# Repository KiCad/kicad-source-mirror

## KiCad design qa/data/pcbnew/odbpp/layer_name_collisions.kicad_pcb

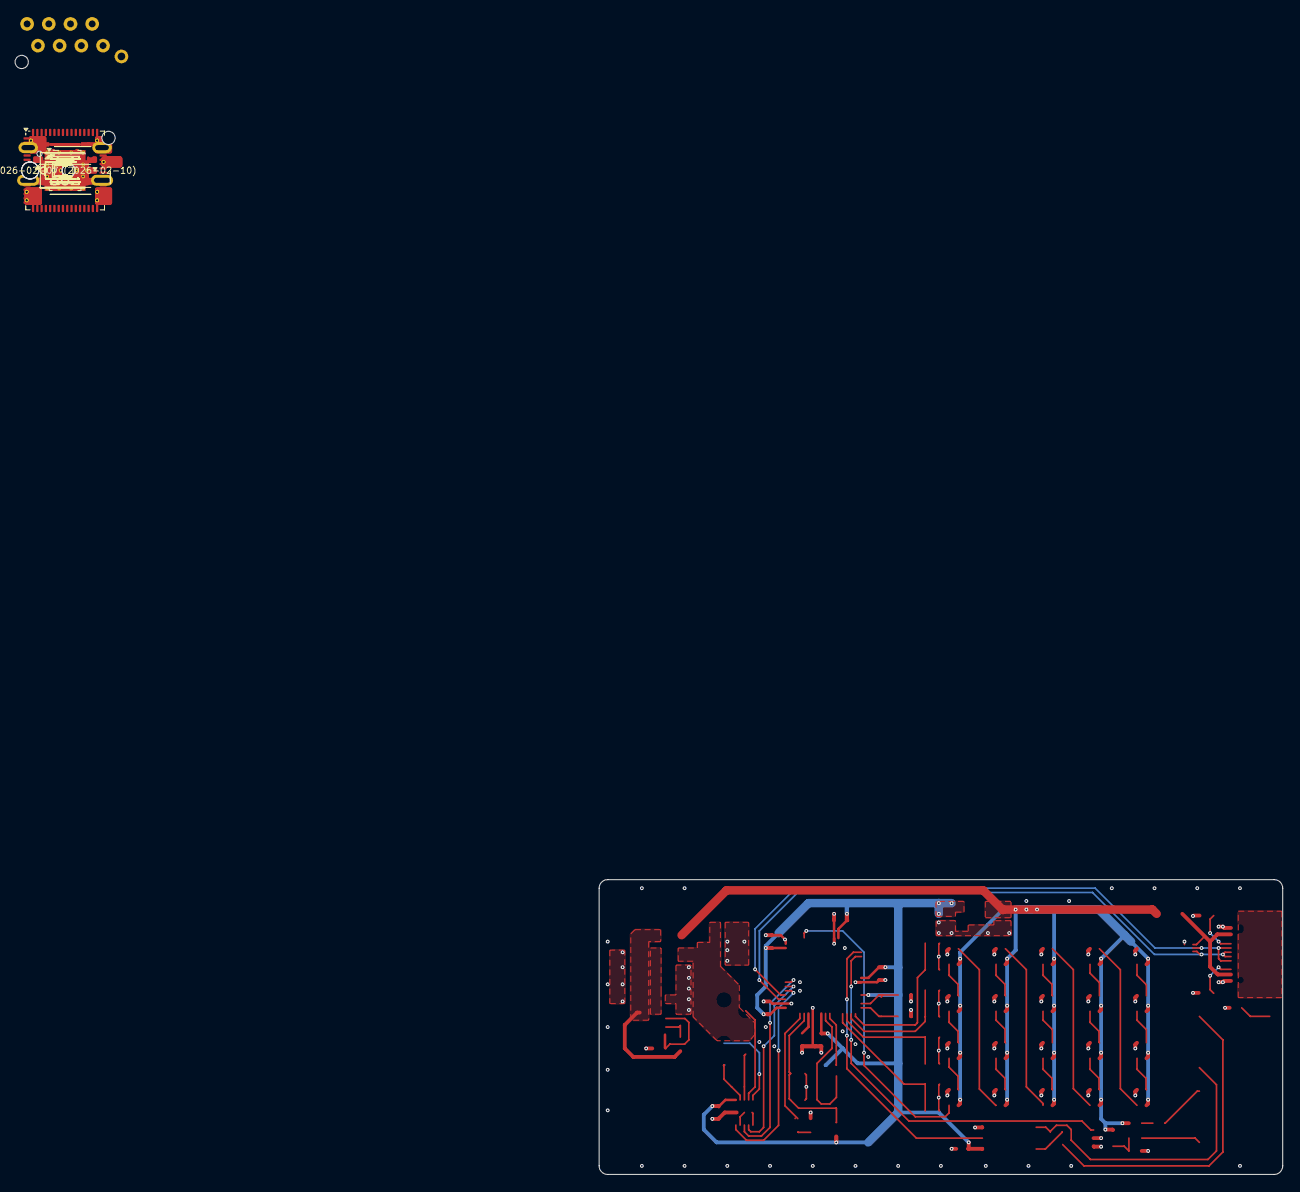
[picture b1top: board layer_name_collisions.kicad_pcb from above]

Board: 4 copper layers, 80.0 x 34.5 mm, 81 parts (1 on the bottom side), 62 nets.

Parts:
C101: 10u; C_0603
C102, C103, C104, C105, C106, C111, C201, C301, C302, C1202: 0u1; C_0603
C107, C110: 18p; C_0603
C108, C109: 10u; C_0805
C1201: 10u; C_1210
C1203, C1204: 22u; C_1210
C1205: 1u; C_0603
D101: Orange; LED_0603
D102, D103, D104: PMEG6030AEXEX; D_SOD-123HP
D301, D401: RB501SM; D_SOD-523
D501, D502, D503, D504, D505, D506, D507, D508, D509, D510, D511, D512, D513, D514, D515, D516, D517, D518, D519, D520: WS2812; WS2812-2020
ESD101: RCLAMP0582N; SLP1210N6
FID101, FID102, FID103: Fiducial_Paste; Fiducial_0.5mm_Mask1mm_Paste
ICON101: V2-logo; Logo_Small
INFO101: Revision
INFO102: Layer_Numbers
J101: Cortex
J102: DX07S016JA3; JAE_DX07S016JA3
J201: NE8FAH
J301, J401: SJ2-25404B-SMT-TR; CUI_SJ2-25404B-SMT-TR
R101: 330R; R_0603
R102, R103: 5k1; R_0603
R104: 100k; R_0603
R201: 100R; R_0603
R301, R401, R402: 220R; R_0603
R1201: 40k2; R_0603
R1202: 10k; R_0603
SW101, SW102, SW103, SW104, SW105: SKSG
TVS101: SMBJ33CA; D_SMB
TVS401: CG0603MLC-05LE; D_0603
U101: TPS78433QWDRBRQ1; VSON-8-1_3x3mm_P0.65_EP1.65x2.4mm
U102: ATSAMD51J; QFN-64-1EP_9x9mm_P0.5mm_EP4.8x4.8mm_ThermalVias
U201: THVD2442; VSON-10-4-1EP_3x3mm_P0.5mm_EP1.65x2.4mm_ThermalVias
U301: TLP2361; SO-5-6_4.55x3.7mm_P1.27mm
U401: 74AHC1G125; SOT-23-5
U1201: TPSM365R6FRDNR; QFN-11
Y101: 32k768; Crystal_SMD_3215-2Pin_3.2x1.5mm

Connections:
+3V3: C102.1, C103.1, C104.1, C105.1, C106.1, C109.1, C201.1, C301.1, J101.1 (VCC), R104.1, U101.1 (OUT), U102.4 (ANAREF), U102.8 (VDDANA), U102.21 (VDDIOB), U102.34 (VDDIO), U102.48 (VDDIO), U102.56 (VDDIO), U201.10 (VCC), U301.6 (VDD)
+5V: C108.1, D102.1 (K), D103.1 (K), D501.4 (VCC), D502.4 (VCC), D503.4 (VCC), D504.4 (VCC), D505.4 (VCC), D506.4 (VCC), D507.4 (VCC), D508.4 (VCC), D509.4 (VCC), D510.4 (VCC), D511.4 (VCC), D512.4 (VCC), D513.4 (VCC), D514.4 (VCC), D515.4 (VCC), D516.4 (VCC), D517.4 (VCC), D518.4 (VCC), D519.4 (VCC), D520.4 (VCC), R401.2, U101.7 (EN), U101.8 (IN), U401.5
+VLINK: C111.1, D104.2 (A), J201.4, J201.5, TVS101.2 (A)
/+5V-Link: C1203.1, C1204.1, D103.2 (A), R1201.1, U1201.4 (VOUT)
/+VBUS: D102.2 (A), ESD101.6 (VBUS), J102.V (VBUS)
/+VLINK-Supply: C1201.1, C1202.1, D104.1 (K), U1201.2 (EN), U1201.3 (VIN)
/Button-1: SW101.2, U102.61 (PB00)
/Button-2: SW102.2, U102.62 (PB01)
/Button-3: SW103.2, U102.63 (PB02)
/Button-4: SW104.2, U102.64 (PB03)
/LED-Onboard: D101.2 (A), U102.51 (PA27)
/LEDs: D501.3 (IN), U102.29 (PA12)
/LEDs/LED-5: D504.1 (OUT), D505.3 (IN)
/LEDs/LED-9: D508.1 (OUT), D509.3 (IN)
/LEDs/LED-13: D512.1 (OUT), D513.3 (IN)
/LEDs/LED-17: D516.1 (OUT), D517.3 (IN)
/Link Socket/RX-A: J201.1, R201.1, U201.9 (A)
/Link Socket/RX-B: J201.2, R201.2, U201.8 (B)
/Link Socket/TX-Y: J201.3, U201.6 (Y)
/Link Socket/TX-Z: J201.6, U201.7 (Z)
/MIDI In/Ring: J301.3 (R1), R301.1
/MIDI In/Sleeve: C302.1, J301.1 (S)
/MIDI In/Tip: D301.2 (A), J301.2 (T), U301.3 (K)
/MIDI Out/Ring: D401.1 (K), J401.3 (R1)
/MIDI Out/Tip: J401.2 (T), R402.2
/MIDI-In: U102.14 (PA05), U301.5 (VO)
/MIDI-Out: U102.13 (PA04), U401.1
/Power +5V/Feedback: R1201.2, R1202.1, U1201.9 (FB)
/Power +5V/Vcc: C1205.1, U1201.8 (VCC), U1201.11 (MODE)
/RESET: J101.10 (RESET), R104.2, SW105.2, U102.52 (~RESET)
/SWCLK: J101.4 (SWCLK), U102.57 (PA30)
/SWDIO: J101.2 (SWDIO), U102.58 (PA31)
/Socket-RX: U102.44 (PA23), U201.1 (R)
/Socket-TX: U102.43 (PA22), U201.4 (D)
/Socket-TX-Enable: U102.42 (PA21), U201.3 (DE)
/USB+: ESD101.4 (I/O1), J102.A6 (D+), J102.B6 (D+), U102.46 (USB+)
/USB-: ESD101.5 (I/O2), J102.A7 (D-), J102.B7 (D-), U102.45 (USB-)
/USB-CC1: J102.A5 (CC1), R102.1
/USB-CC2: J102.B5 (CC2), R103.1
/VDDCORE: C101.1, U102.53 (VDDCORE)
/XIN32: C107.1, U102.1 (PA00), Y101.2
/XOUT32: C110.1, U102.2 (PA01), Y101.1
GND: C101.2, C102.2, C103.2, C104.2, C105.2, C106.2, C107.2, C108.2, C109.2, C110.2, C111.2, C201.2, C301.2, C302.2, C1201.2, C1202.2, C1203.2, C1204.2, C1205.2, D501.2 (GND), D502.2 (GND), D503.2 (GND), D504.2 (GND), D505.2 (GND), D506.2 (GND), D507.2 (GND), D508.2 (GND), D509.2 (GND), D510.2 (GND), D511.2 (GND), D512.2 (GND), D513.2 (GND), D514.2 (GND), D515.2 (GND), D516.2 (GND), D517.2 (GND), D518.2 (GND), D519.2 (GND), D520.2 (GND), ESD101.1 (GND), J101.3 (GND), J101.5 (GND), J102.G (GND), J201.7, J201.8, J401.1 (S), R101.2, R102.2, R103.2, R1202.2, SW101.1, SW102.1, SW103.1, SW104.1, SW105.1, TVS101.1 (K), TVS401.1 (K), U101.5 (GND), U101.9 (GND), U102.7 (GNDANA), U102.22 (GND), U102.33 (GND), U102.47 (GND), U102.54 (GND), U102.65 (PAD), U201.2 (RE), U201.5 (GND), U201.11 (GND), U301.4 (GND), U401.2, U401.3, U1201.10 (GND)
unnamed: D101.1 (K), R101.1
unnamed: D301.1 (K), R301.2, U301.1 (A)
unnamed: D401.2 (A), R401.1
unnamed: D501.1 (OUT), D502.3 (IN)
unnamed: D502.1 (OUT), D503.3 (IN)
unnamed: D503.1 (OUT), D504.3 (IN)
unnamed: D505.1 (OUT), D506.3 (IN)
unnamed: D506.1 (OUT), D507.3 (IN)
unnamed: D507.1 (OUT), D508.3 (IN)
unnamed: D509.1 (OUT), D510.3 (IN)
unnamed: D510.1 (OUT), D511.3 (IN)
unnamed: D511.1 (OUT), D512.3 (IN)
unnamed: D513.1 (OUT), D514.3 (IN)
unnamed: D514.1 (OUT), D515.3 (IN)
unnamed: D515.1 (OUT), D516.3 (IN)
unnamed: D517.1 (OUT), D518.3 (IN)
unnamed: D518.1 (OUT), D519.3 (IN)
unnamed: D519.1 (OUT), D520.3 (IN)
unnamed: R402.1, TVS401.2 (A), U401.4

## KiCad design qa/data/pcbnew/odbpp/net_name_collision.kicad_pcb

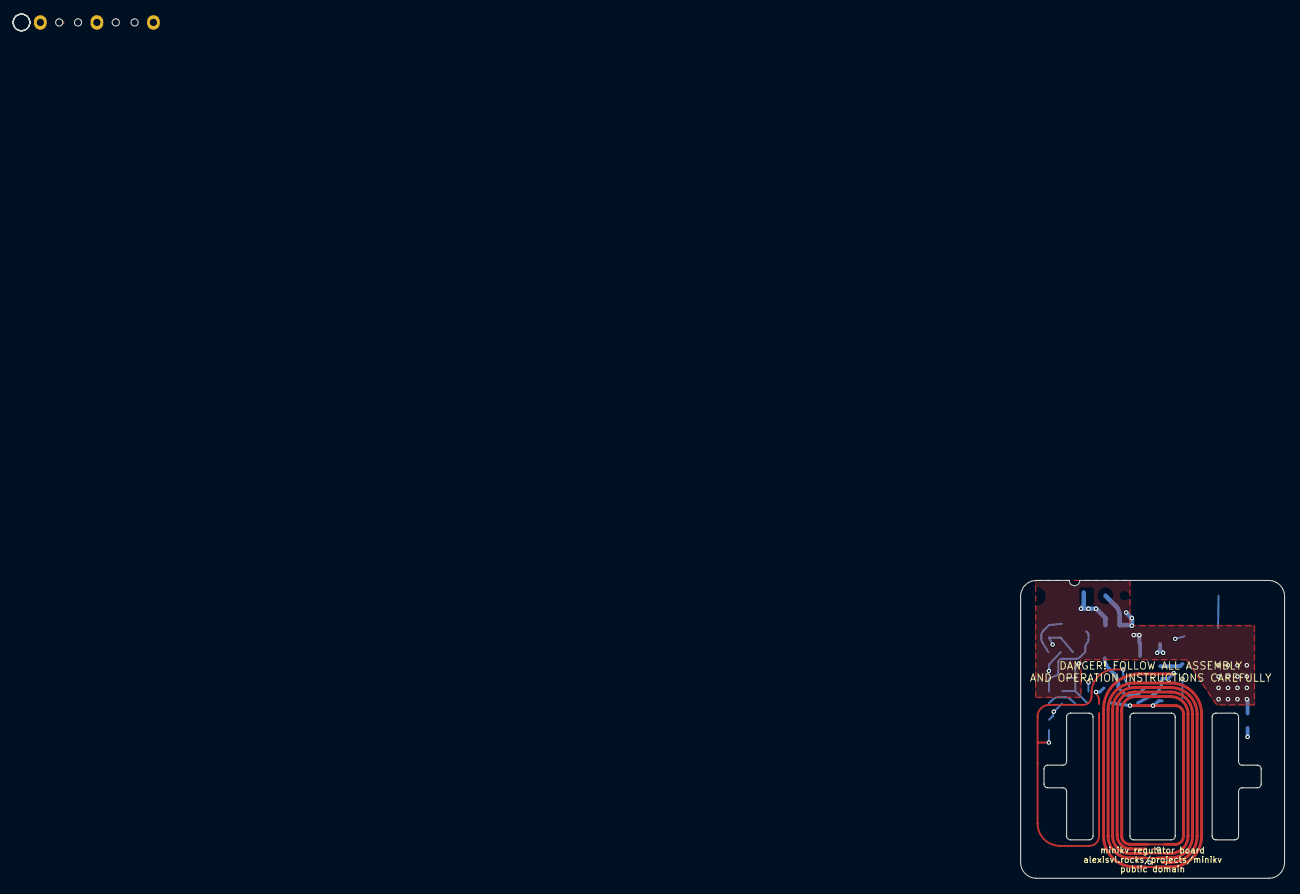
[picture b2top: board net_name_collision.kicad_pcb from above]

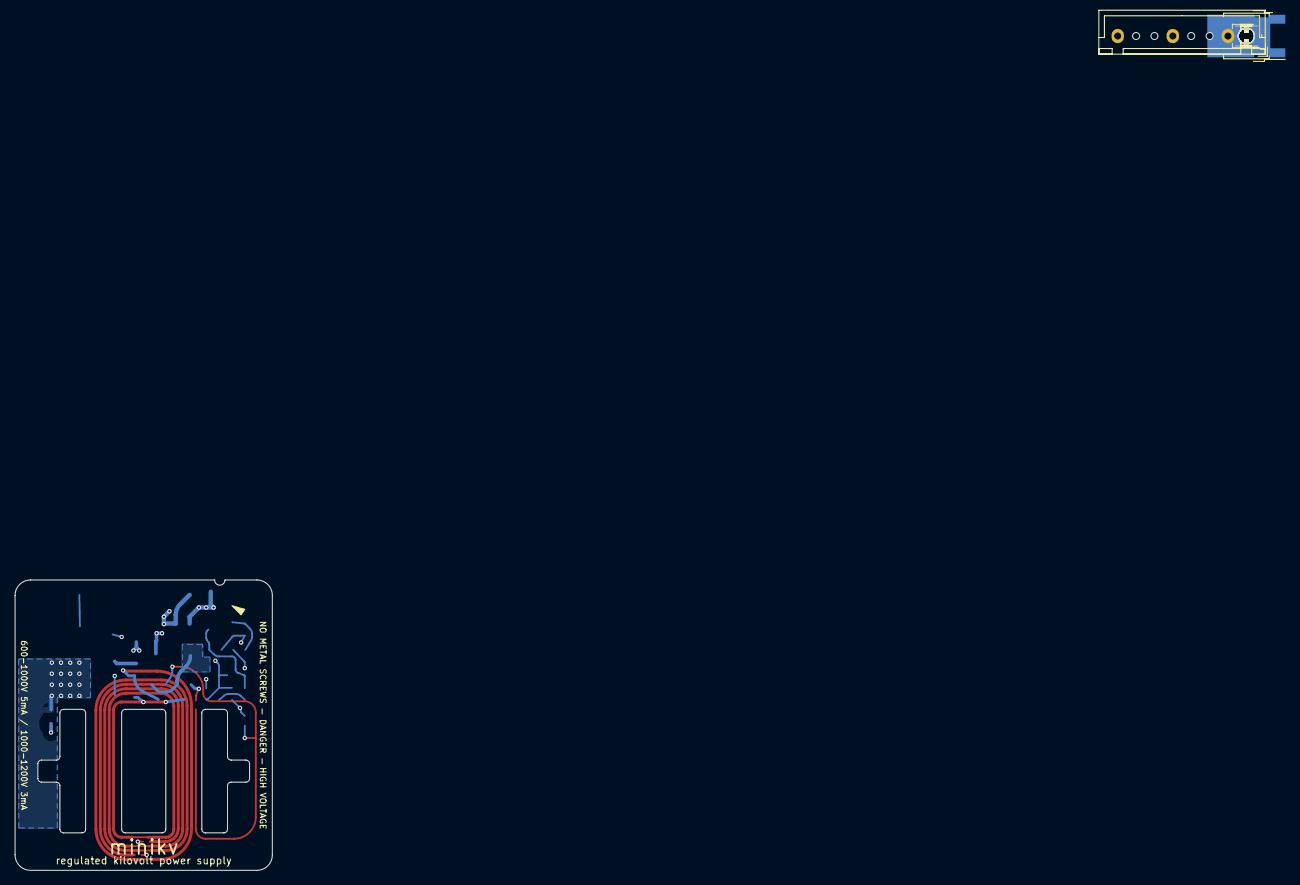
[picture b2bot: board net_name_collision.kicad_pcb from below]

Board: 4 copper layers, 35.0 x 39.5 mm, 27 parts (20 on the bottom side), 15 nets.

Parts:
C1: 15n; C_1206_3216Metric
C2, C3: 1u; C_0805_2012Metric
C4: 390p; C_0603_1608Metric
C5: 220n; C_0603_1608Metric
H1, H2, H3, H4: MountingHole; MountingHole_2.2mm_M2
J1: Conn_01x08; JST_XH_B8B-XH-A_1x08_P2.50mm_Vertical
L1: 220u; L_Bourns_SRN6045TA
Q1, Q2: PBSS8110; SOT-23
Q3: PJD25N03; TO-252-2
R1: 10M; R_2010_5025Metric
R2, R6: 15k; R_0603_1608Metric
R3: 9k1; R_0603_1608Metric
R4: 100k; R_0603_1608Metric
R5: 3M3; R_0603_1608Metric
R7: 1k; R_0805_2012Metric
R8: 1r; R_1210_3225Metric
RV1: 100k; Potentiometer_Bourns_TC33X_Vertical
TW1, TW2: 2½T; NetTie-0.4mm
TW3: ½T; NetTie-0.2mm-1mmClear
U1: TLV431; SOT-23-5

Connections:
+12V: C2.1, C3.1, J1.1, R6.1, R7.1, TW1.2, TW2.1
/1kV: J1.8, R1.1
/RoyerReg: C3.2, L1.2, Q3.2 (D)
GND: C2.2, C5.2, J1.2, R3.2, R8.2, U1.5 (A)
unnamed: C4.2, R5.1
unnamed: C1.1, Q1.3 (C), TW1.1
unnamed: L1.1, Q1.2 (E), Q2.2 (E)
unnamed: C1.2, Q2.3 (C), TW2.2
unnamed: C5.1, Q3.1 (G), R5.2, R6.2, U1.3 (K)
unnamed: Q3.3 (S), R8.1
unnamed: R2.2, R3.1, RV1.3
unnamed: R1.2, R2.1, R4.1, RV1.1
unnamed: C4.1, R4.2, RV1.2, U1.4 (R)
Q B: Q1.1 (B), R7.2, TW3.1
Q_B: Q2.1 (B), TW3.2

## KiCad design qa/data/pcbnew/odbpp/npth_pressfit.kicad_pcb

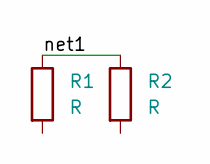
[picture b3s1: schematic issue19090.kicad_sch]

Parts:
R1, R2: R; R_0805_2012Metric

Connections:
/A: R1.1, R2.1
GND: R1.2, R2.2

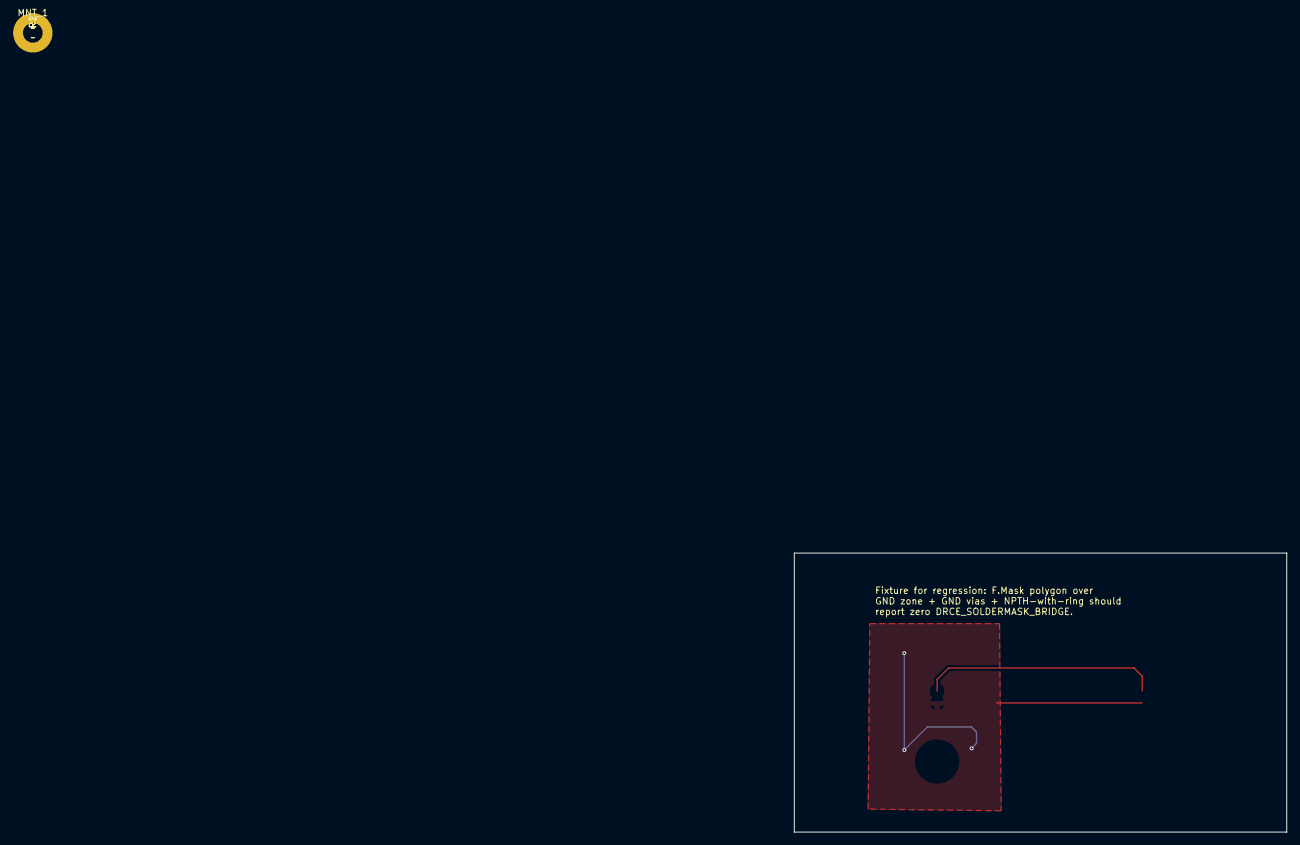
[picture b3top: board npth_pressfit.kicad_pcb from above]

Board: 2 copper layers, 75.0 x 42.5 mm, 3 parts (0 on the bottom side), 2 nets.

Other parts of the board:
MNT_1: MountingHole_2.1mm

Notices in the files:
qa/data/pcbnew/odbpp/net_name_collision.kicad_pcb:
public domain
